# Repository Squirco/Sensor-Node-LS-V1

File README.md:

#Squirco Sensor Network Light Switch

Hardware files for Squirco Sensor Network Light Switch, as seen on Hackaday here:  
https://hackaday.io/project/3321-squirco-smart-home-system-sensor-network  
  
#Repository Contents
* **/Hardware-Main** - Eagle design files for the Logic and Power Supply boards (.sch and .brd)
* **/Hardware-Addon** - Eagle design files for the button, sensor, and programming adaptor boards (.sch and .brd)
* **/Hardware-3D** - 3D files for the enclosure. Designed to be 3D printed, tested with Form1+ and Shapeways/Sculpteo
* **/Hardware-Extras** - Contains BOM and other documents
* **/Firmware** - contains firmware files
  
#License Information
The hardware is released under <a href = "https://creativecommons.org/licenses/by-sa/4.0/">CC BY-SA 4.0</a>  
Hardware authors: Original Design by Steven @ Squirco
Distributed as-is; no warranty is given

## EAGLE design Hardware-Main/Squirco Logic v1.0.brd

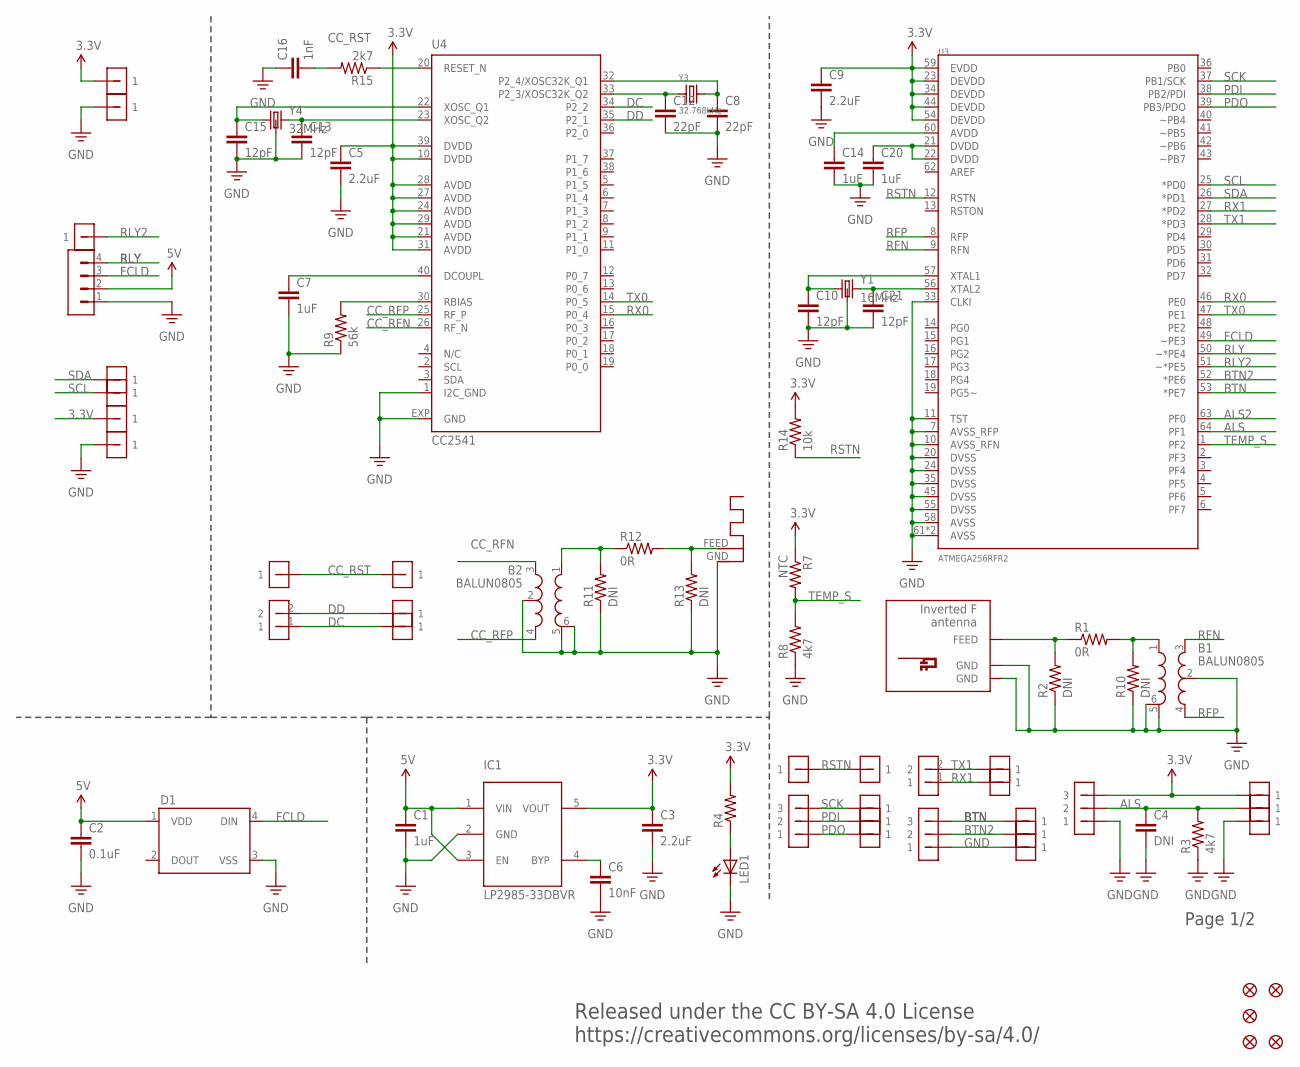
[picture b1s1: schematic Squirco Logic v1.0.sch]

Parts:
ANT1: ANTENNA; RN-ANT
ANT2: INVERTED_F_ANTENNA+5; DN007+5
B1, B2: BALUN0805; BALUN-2-4GHZ
C1, C7, C14, C20: 1uF; 0603-CAP
C2: 0.1uF; 0603-CAP
C3, C5, C9: 2.2uF; 0603-CAP
C4: DNI; 0603-CAP
C6: 10nF; 0603-CAP
C8, C12: 22pF; 0402-CAP
C10, C13, C15, C21: 12pF; 0402-CAP
C16: 1nF; 0603-CAP
D1: WS2812B
FID1, FID2, FID3, FID5, FID6: FIDUCIALUFIDUCIAL; MICRO-FIDUCIAL
IC1: LP2985-33DBVR; SOT23-5L
JP1: M02
LED1: LEDCHIP-LED0805; CHIP-LED0805
R1, R12: 0R; R0402
R2, R10, R11, R13: DNI; R0402
R3, R8: 4k7; R0603
R4: RESISTOR0603; 0603-RES
R7: NTC; R0402
R9: 56k; R0603
R14: 10k; R0603
R15: 2k7; R0603
U3: ATMEGA256RFR2; QFN-64
U4: CC2541; RHA_S-PVQFN-N40
U$4, U$6, U$25: M03
U$5: S04-4MM
U$7, U$8: M01
U$9: M02
U$10, U$11, U$12, U$13, U$14, U$15, U$16, U$17, U$18, U$19, U$20, U$21, U$22, U$23, U$24, U$26, U$27, U$30, U$31, U$34: S01C-4MM
U$32, U$33: S01-4MM
Y1: 16MHz; CRYSTAL-SMD-2.5X2-ABM10
Y3: 32.768kHz; ABS07
Y4: 32MHz; CRYSTAL-SMD-2.5X2-ABM10

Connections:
3.3V: C3.1, C5.1, C9.1, IC1.5 (VOUT), R4.2, R7.1, R14.2, U3.23 (DEVDD), U3.34 (DEVDD), U3.44 (DEVDD), U3.54 (DEVDD), U3.59 (EVDD), U4.10 (DVDD), U4.21 (AVDD), U4.24 (AVDD), U4.27 (AVDD), U4.28 (AVDD), U4.29 (AVDD), U4.31 (AVDD), U4.39 (DVDD), U$20.P$1, U$25.3, U$26.P$1, U$30.P$1
5V: C1.1, C2.1, D1.1 (VDD), IC1.1 (VIN), IC1.3 (EN), U$5.2
ALS: C4.1, R3.2, U3.64 (PF1), U$25.2, U$31.P$1
ALS2: U3.63 (PF0)
BTN: U3.53 (*PE7), U$6.3, U$22.P$1
BTN2: U3.52 (*PE6), U$6.2, U$23.P$1
CC_RFN: B2.3, U4.26 (RF_N)
CC_RFP: B2.4, U4.25 (RF_P)
CC_RST: C16.2, R15.2, U$8.1, U$17.P$1
DC: U4.34 (P2_2), U$9.1, U$19.P$1
DD: U4.35 (P2_1), U$9.2, U$18.P$1
FCLD: D1.4 (DIN), U3.49 (~PE3), U$5.3
GND: ANT1.GND, ANT2.GND, ANT2.GND@1 (GND), B1.2, B1.5, B1.6, B2.2, B2.5, B2.6, C1.2, C2.2, C3.2, C4.2, C5.2, C6.2, C7.2, C8.2, C9.2, C10.2, C12.2, C13.2, C14.2, C15.2, C16.1, C20.2, C21.2, D1.3 (VSS), IC1.2 (GND), LED1.C, R2.1, R3.1, R8.1, R9.1, R10.1, R11.1, R13.1, U3.7 (AVSS_RFP), U3.10 (AVSS_RFN), U3.11 (TST), U3.20 (DVSS), U3.24 (DVSS), U3.33 (CLKI), U3.35 (DVSS), U3.45 (DVSS), U3.55 (DVSS), U3.58 (AVSS), U3.61 (AVSS), U3.PADDLE (AVSS), U4.1 (I2C_GND), U4.EXP (GND), U$5.1, U$6.1, U$21.P$1, U$25.1, U$27.P$1, U$32.P$1, U$33.P$1, Y1.P$2 (GND), Y1.P$4 (GND), Y4.P$2 (GND), Y4.P$4 (GND)
unnamed: C10.1, U3.57 (XTAL1), Y1.P$1 (1)
unnamed: C21.1, U3.56 (XTAL2), Y1.P$3 (2)
unnamed: LED1.A, R4.1
unnamed: ANT2.FEED, R1.1, R2.2
unnamed: C6.1, IC1.4 (BYP)
unnamed: C7.1, U4.40 (DCOUPL)
unnamed: C20.1, U3.21 (DVDD), U3.22 (DVDD)
unnamed: C14.1, U3.60 (AVDD)
unnamed: R9.2, U4.30 (RBIAS)
unnamed: B2.1, R11.2, R12.1
unnamed: ANT1.FEED, R12.2, R13.2
unnamed: C15.1, U4.22 (XOSC_Q1), Y4.P$1 (1)
unnamed: C13.1, U4.23 (XOSC_Q2), Y4.P$3 (2)
unnamed: C8.1, U4.32 (P2_4/XOSC32K_Q1), Y3.2
unnamed: B1.1, R1.2, R10.2
unnamed: C12.1, U4.33 (P2_3/XOSC32K_Q2), Y3.1
unnamed: R15.1, U4.20 (RESET_N)
N/C: U4.4 (N/C)
PDI: U3.38 (PB2/PDI), U$4.2, U$13.P$1
PDO: U3.39 (PB3/PDO), U$4.1, U$14.P$1
RFN: B1.3, U3.9 (RFN)
RFP: B1.4, U3.8 (RFP)
RLY: U3.50 (~*PE4), U$5.4
RLY2: U3.51 (~*PE5), U$34.P$1
RSTN: R14.1, U3.12 (RSTN), U$7.1, U$11.P$1
RX0: U3.46 (PE0), U4.15 (P0_4)
RX1: JP1.1, U3.27 (*PD2), U$16.P$1
SCK: U3.37 (PB1/SCK), U$4.3, U$12.P$1
SCL: U3.25 (*PD0), U$24.P$1
SDA: U3.26 (*PD1), U$10.P$1
TEMP_S: R7.2, R8.2, U3.1 (PF2)
TX0: U3.47 (PE1), U4.14 (P0_5)
TX1: JP1.2, U3.28 (*PD3), U$15.P$1

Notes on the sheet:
Page 1/2
Released under the CC BY-SA 4.0 License https://creativecommons.org/licenses/by-sa/4.0/

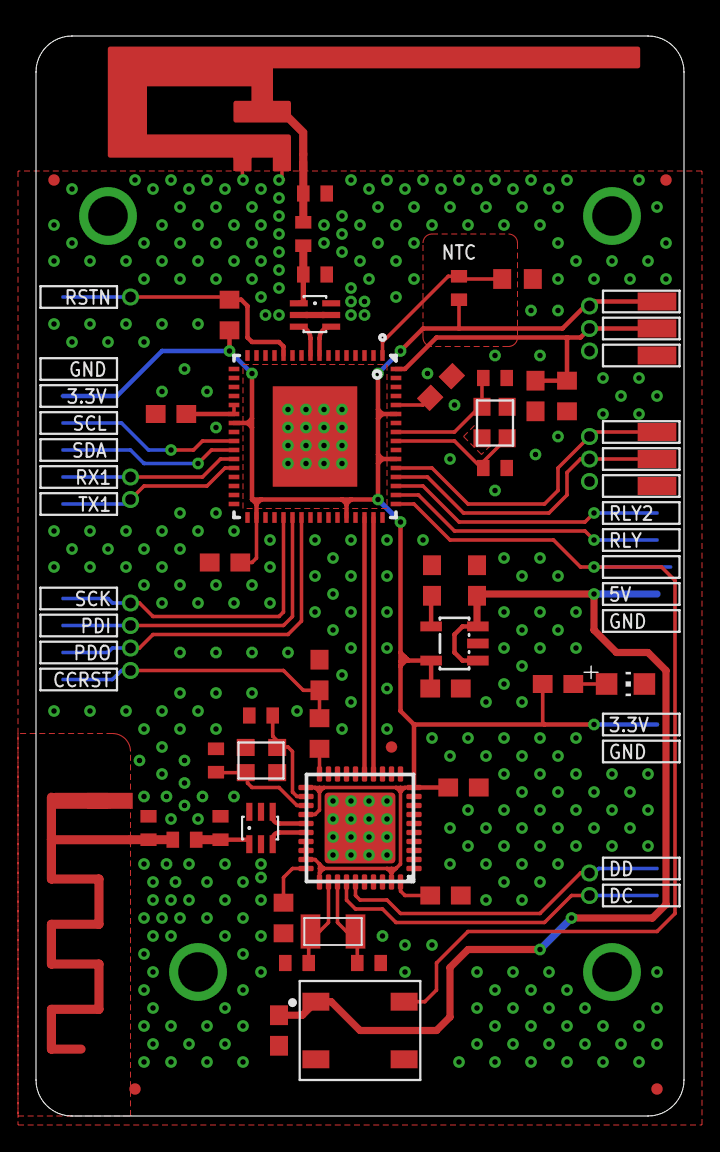
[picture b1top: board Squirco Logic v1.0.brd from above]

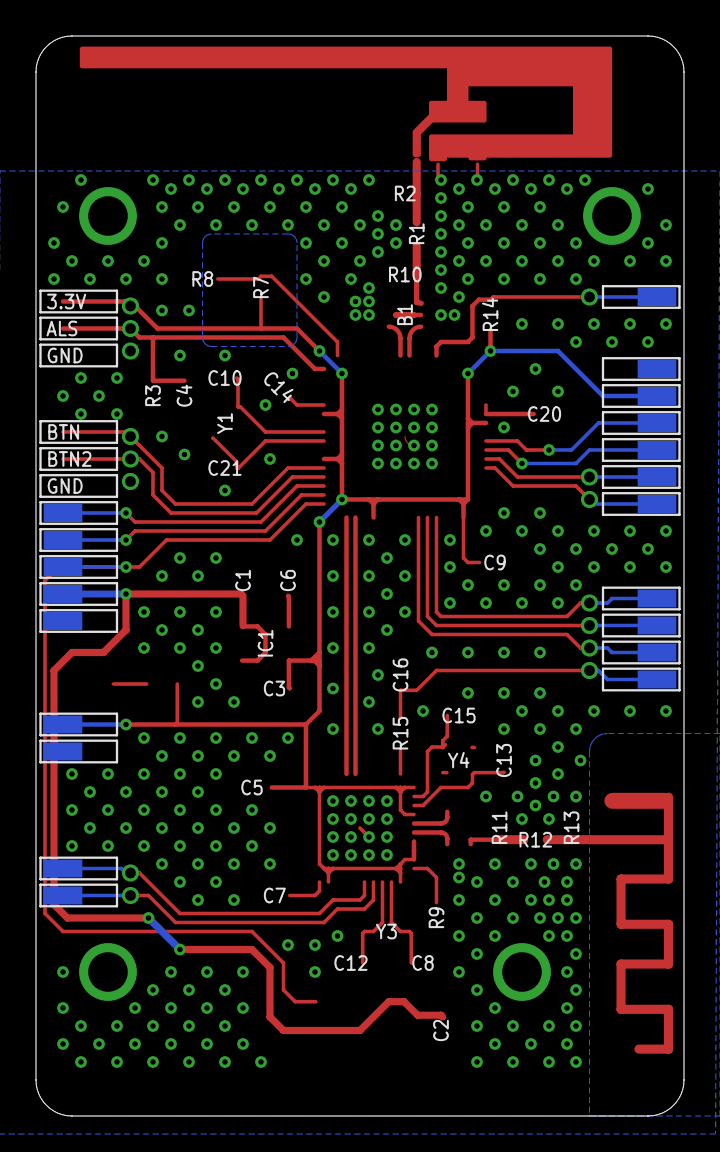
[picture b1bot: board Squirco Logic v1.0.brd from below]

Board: 2 copper layers, 36.0 x 60.0 mm, 77 parts (17 on the bottom side), 44 nets.

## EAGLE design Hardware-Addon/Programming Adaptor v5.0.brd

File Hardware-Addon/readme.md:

#Squirco Sensor Light Switch Addons
Button board is designed for 1.6mm thickness. Ambient light sensor board is designed for 1.6mm thickness or below, ideally as thin as possible.

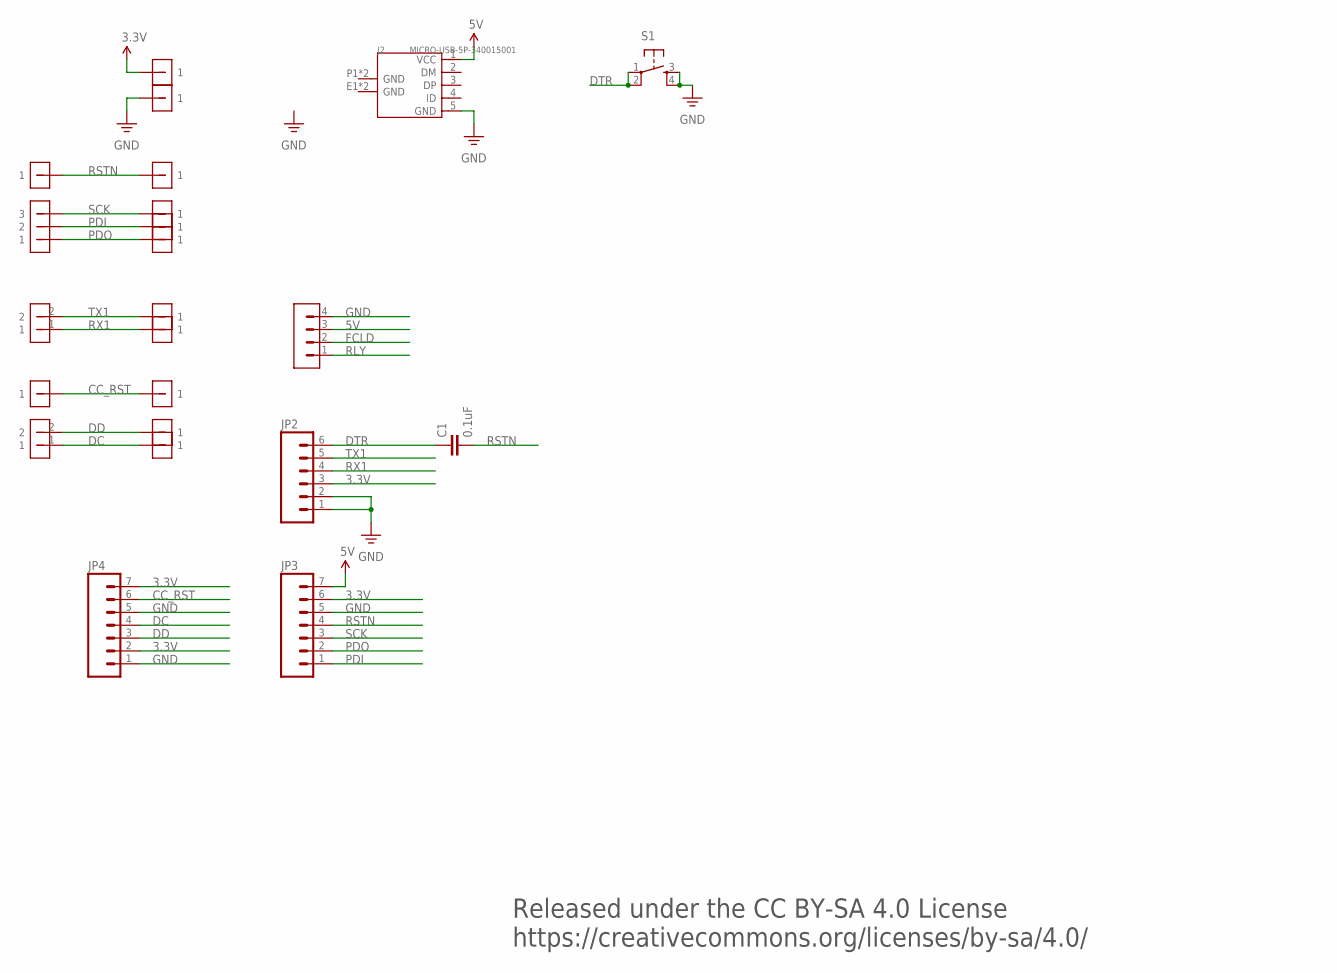
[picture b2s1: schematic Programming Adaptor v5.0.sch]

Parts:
C1: 0.1uF; 0603-CAP
J2: MICRO-USB-5P-340015001; B-SMD-5P
JP1: M02
JP2: M06LOCK; 1X06_LOCK
JP3, JP4: M07; 1X07
S1: TAC_SWITCHSMD; TACTILE-SWITCH-SMD
U$4: M03
U$5: S04-4MM
U$7, U$8: M01
U$9: M02
U$11, U$12, U$13, U$14, U$15, U$16, U$17, U$18, U$19, U$20, U$21: S01C-4MM

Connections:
3.3V: JP2.3, JP3.6, JP4.2, JP4.7, U$20.P$1
5V: J2.1 (VCC), JP3.7, U$5.3
CC_RST: JP4.6, U$8.1, U$17.P$1
DC: JP4.4, U$9.1, U$19.P$1
DD: JP4.3, U$9.2, U$18.P$1
DTR: C1.1, JP2.6, S1.1, S1.2
FCLD: U$5.2
GND: J2.5 (GND), JP2.1, JP2.2, JP3.5, JP4.1, JP4.5, S1.3, S1.4, U$5.4, U$21.P$1
PDI: JP3.1, U$4.2, U$13.P$1
PDO: JP3.2, U$4.1, U$14.P$1
RLY: U$5.1
RSTN: C1.2, JP3.4, U$7.1, U$11.P$1
RX1: JP1.1, JP2.4, U$16.P$1
SCK: JP3.3, U$4.3, U$12.P$1
TX1: JP1.2, JP2.5, U$15.P$1

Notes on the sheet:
Released under the CC BY-SA 4.0 License https://creativecommons.org/licenses/by-sa/4.0/

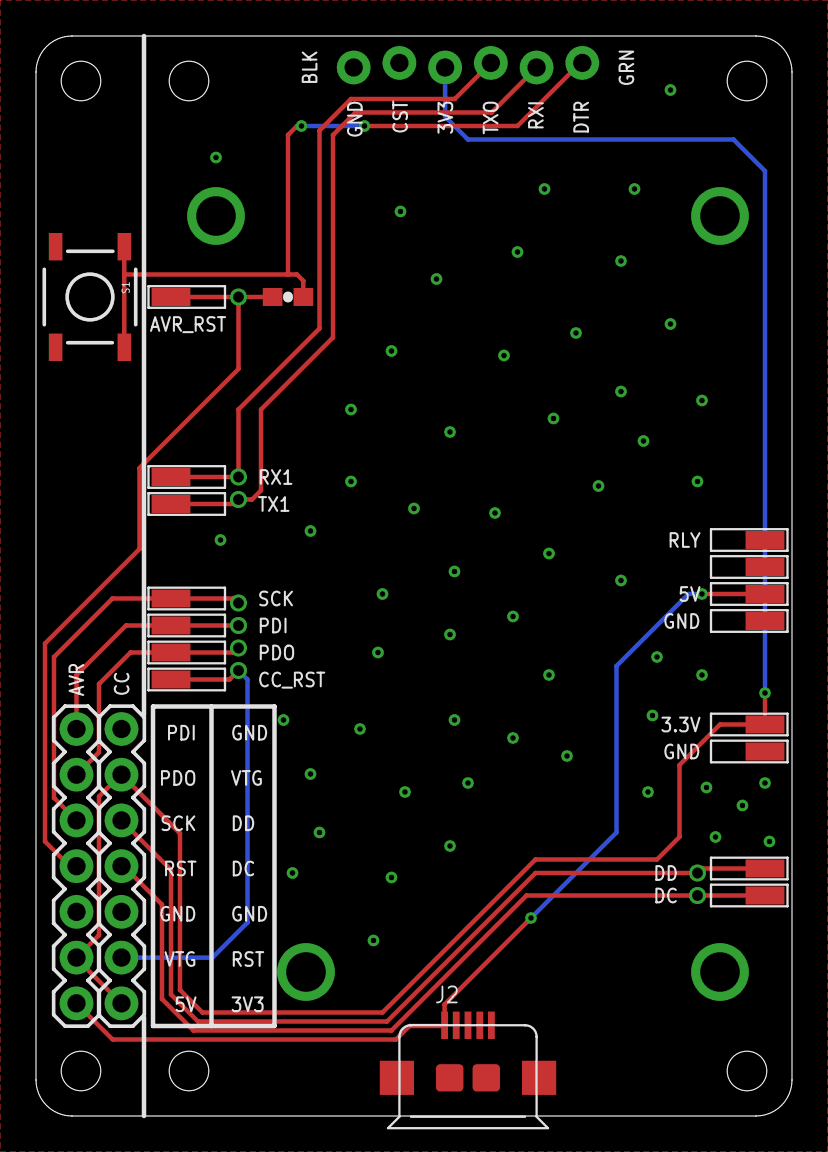
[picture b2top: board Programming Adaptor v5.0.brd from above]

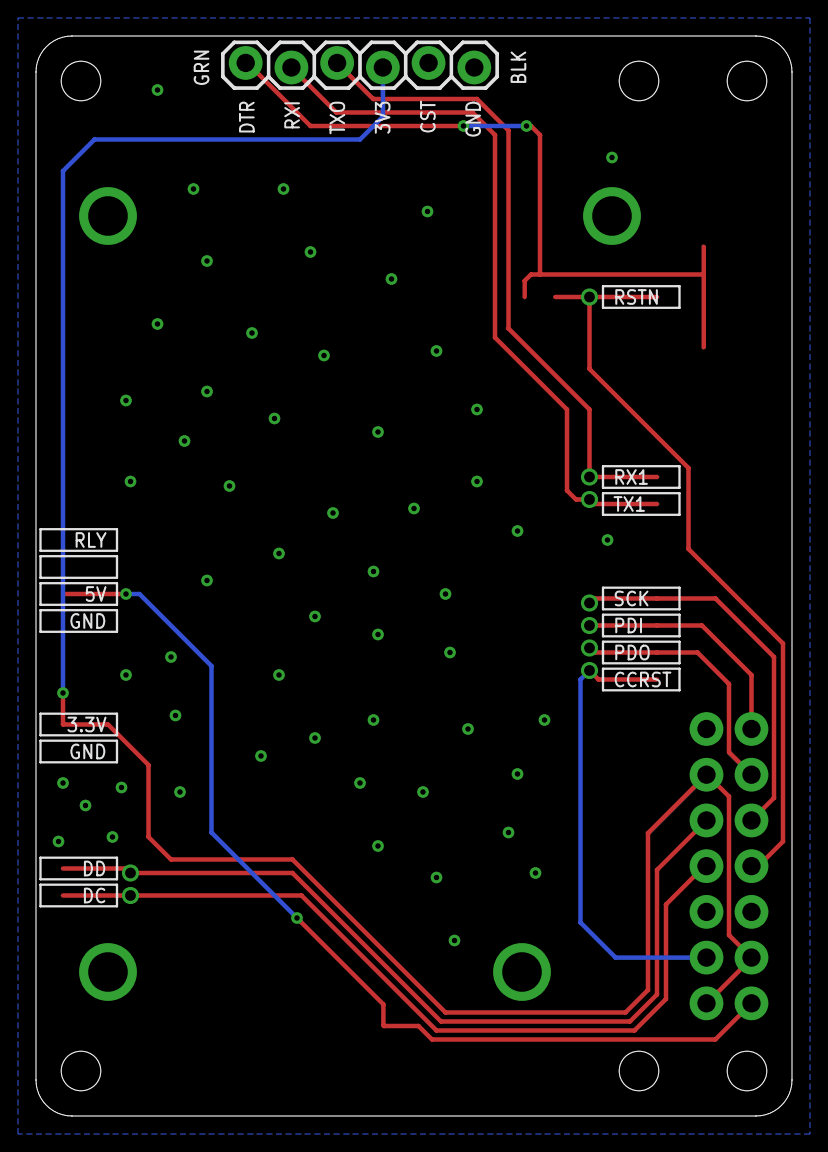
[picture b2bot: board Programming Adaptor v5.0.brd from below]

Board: 2 copper layers, 42.0 x 60.0 mm, 23 parts (2 on the bottom side), 13 nets.

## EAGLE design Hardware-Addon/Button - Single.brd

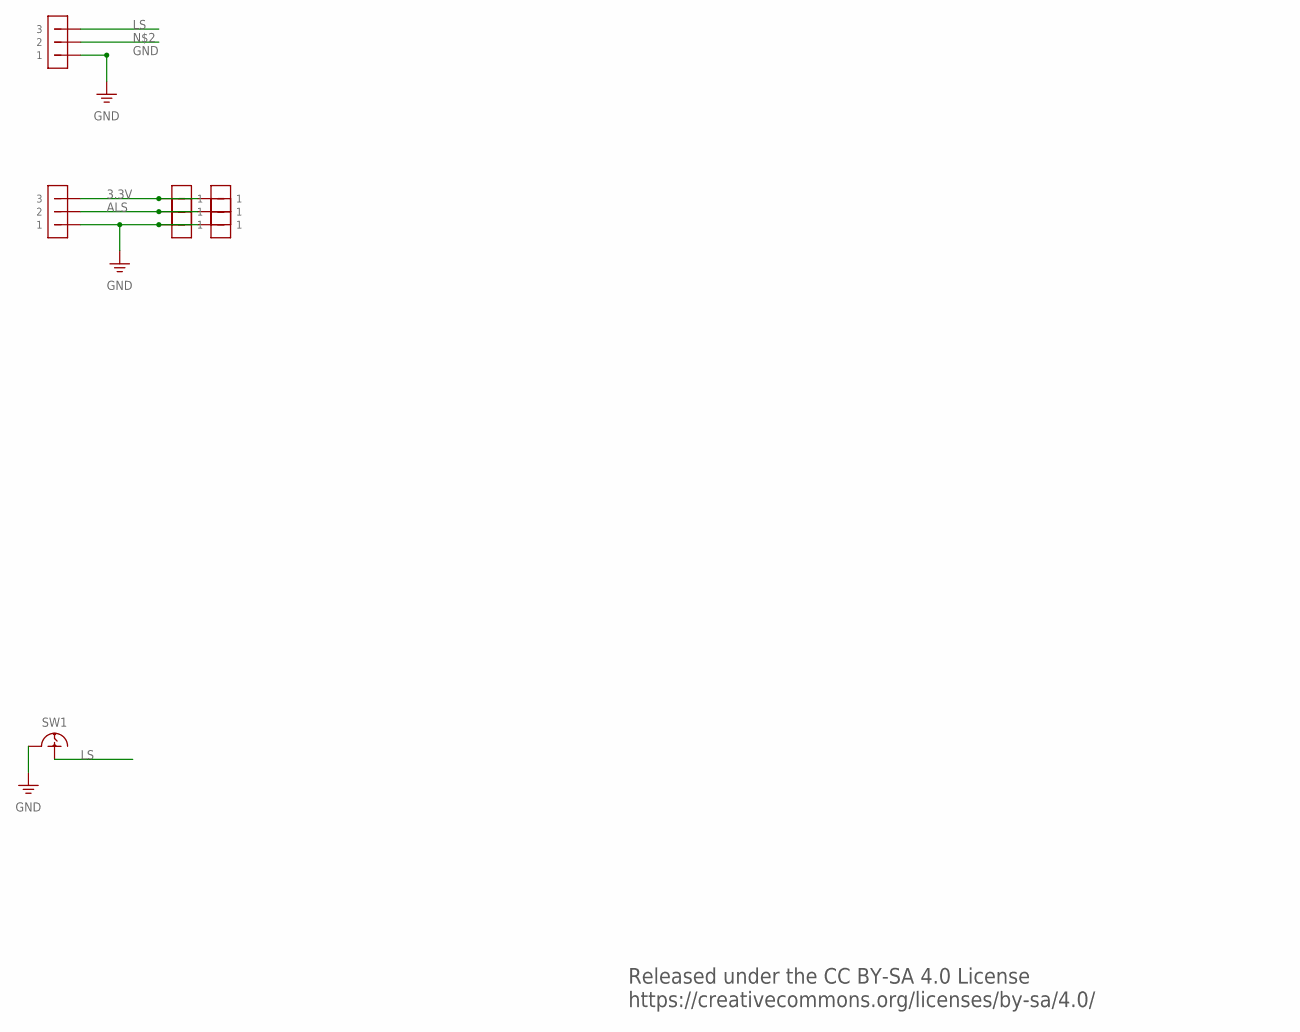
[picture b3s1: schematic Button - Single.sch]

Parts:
SW1: U12390; UFTCGX12
U$1, U$2: M03
U$3, U$4, U$5, U$6, U$7, U$8: S01-4MM

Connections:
3.3V: U$1.3, U$3.P$1, U$6.P$1
ALS: U$1.2, U$4.P$1, U$7.P$1
GND: SW1.GND, U$1.1, U$2.1, U$5.P$1, U$8.P$1
LS: SW1.SIG, U$2.3

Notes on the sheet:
Released under the CC BY-SA 4.0 License https://creativecommons.org/licenses/by-sa/4.0/

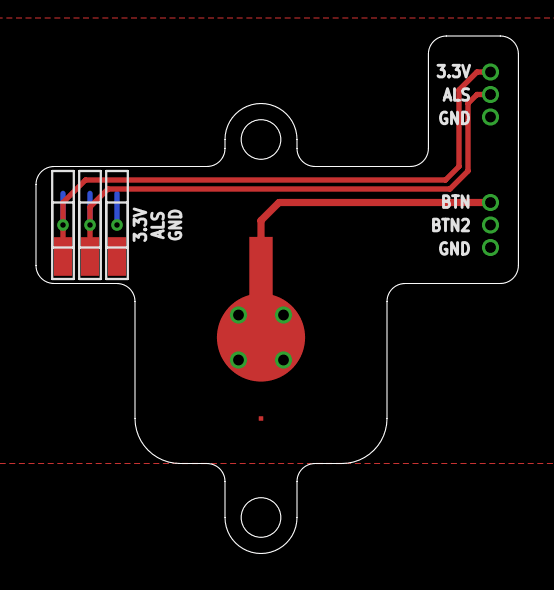
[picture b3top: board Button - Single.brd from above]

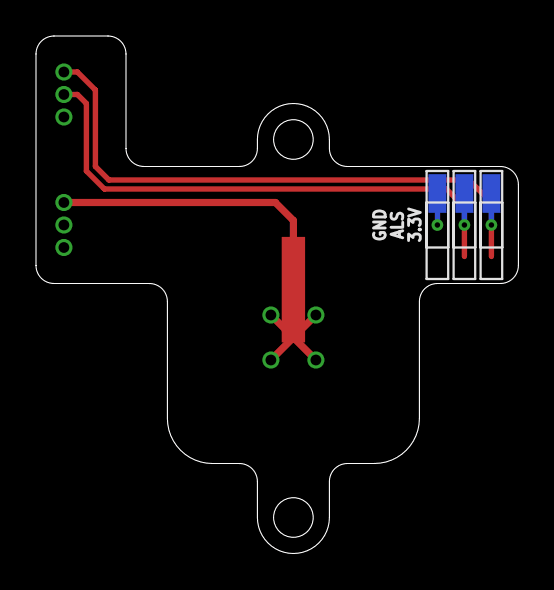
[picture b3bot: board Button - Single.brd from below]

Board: 2 copper layers, 26.8 x 28.8 mm, 9 parts (3 on the bottom side), 4 nets.

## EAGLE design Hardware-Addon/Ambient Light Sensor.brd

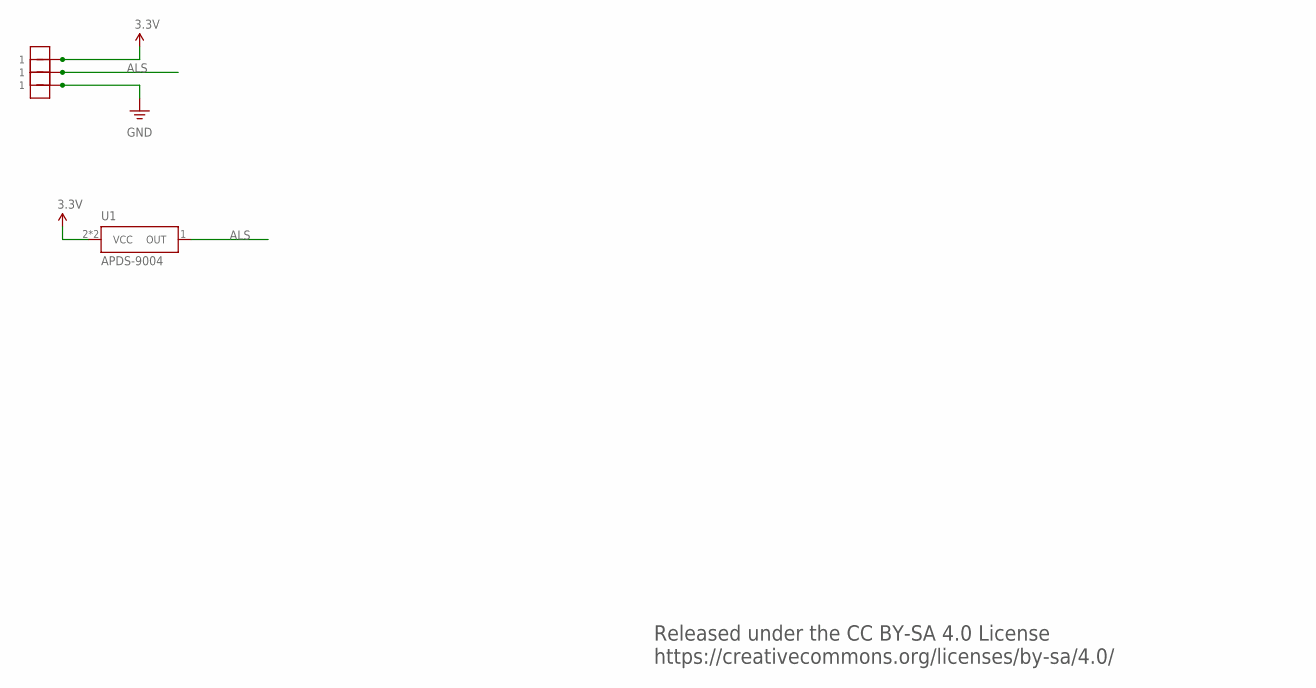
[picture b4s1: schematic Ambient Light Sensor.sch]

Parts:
U1: ADPS-9004; APDS-9004
U$2, U$3, U$4: S01-4MM

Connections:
3.3V: U1.2 (VCC), U1.3 (VCC), U$2.P$1
ALS: U1.1 (OUT), U$3.P$1
GND: U$4.P$1

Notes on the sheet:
Released under the CC BY-SA 4.0 License https://creativecommons.org/licenses/by-sa/4.0/

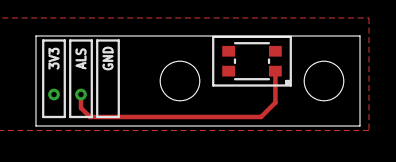
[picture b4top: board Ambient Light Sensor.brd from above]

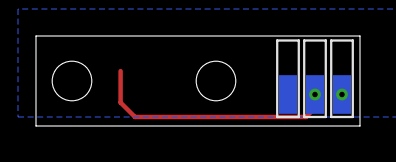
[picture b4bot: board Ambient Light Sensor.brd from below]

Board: 2 copper layers, 18.0 x 5.0 mm, 4 parts (3 on the bottom side), 2 nets.

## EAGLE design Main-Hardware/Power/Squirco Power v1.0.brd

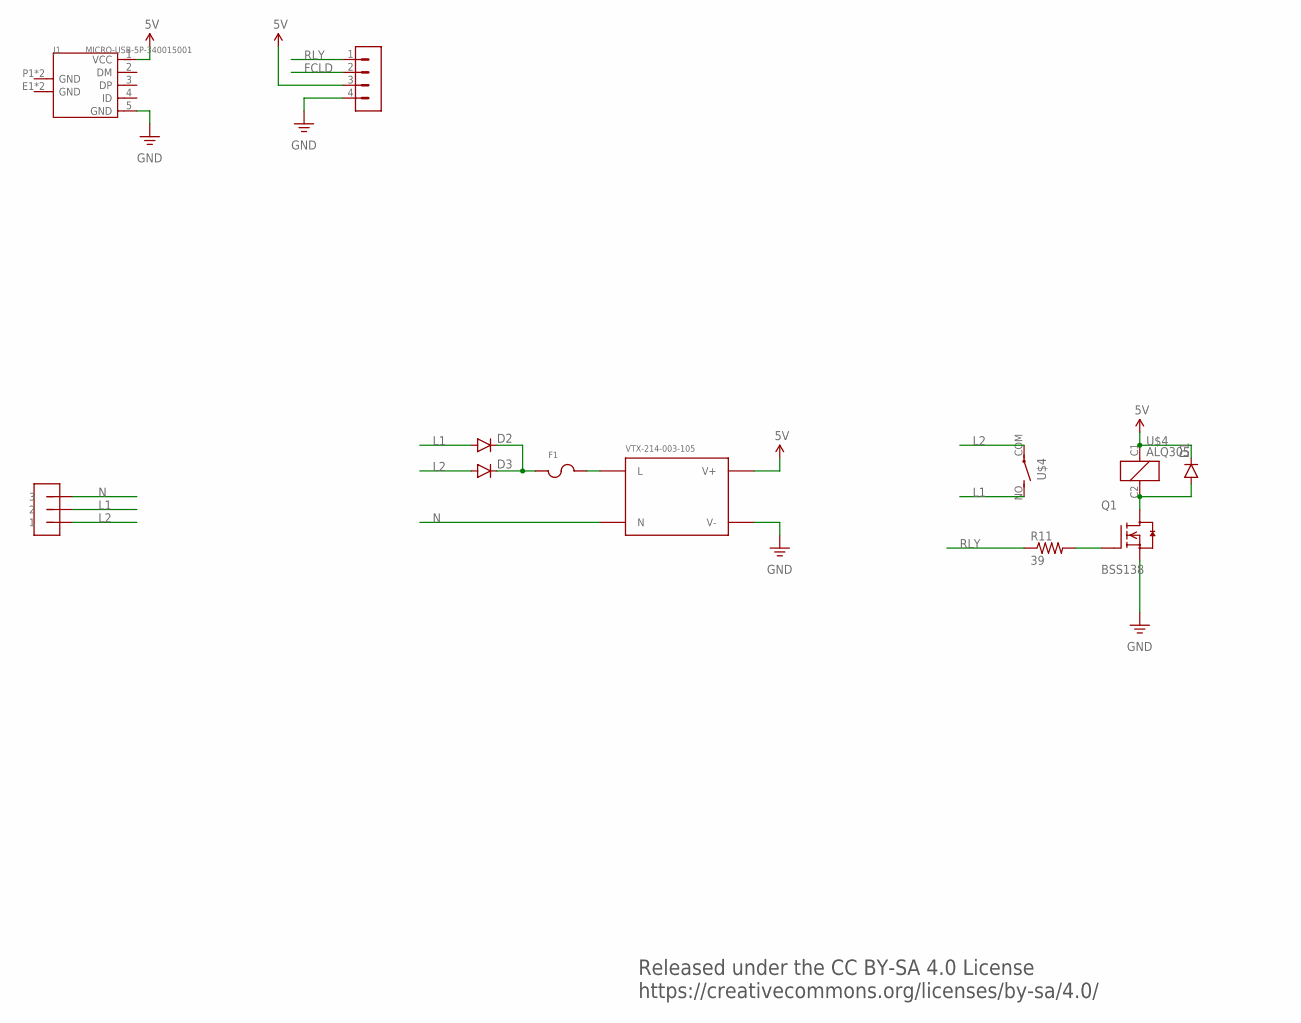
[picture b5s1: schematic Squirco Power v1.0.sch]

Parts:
D1, D2, D3: DIODESMB; SMB-DIODE
F1: UMT250
J1: MICRO-USB-5P-340015001; B-SMD-5P
JP2: LSF-SMT5; LF-SMT5
Q1: BSS138; SOT23
R11: 39; 0603-RES
U$1: VTX-214-003-105; VTX-214-003-1XX
U$3: S04-4MM
U$4: ALQ305

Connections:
5V: D1.C, J1.1 (VCC), U$1.3 (V+), U$3.3, U$4.C1 (1)
FCLD: U$3.2
GND: J1.5 (GND), Q1.2 (S), U$1.4 (V-), U$3.4
L1: D2.A, JP2.3 (2), JP2.4 (2), U$4.NO (S)
L2: D3.A, JP2.1, JP2.2 (1), U$4.COM
N: JP2.5 (3), JP2.6 (3), U$1.1 (N)
unnamed: F1.P$2, U$1.2 (L)
unnamed: Q1.1 (G), R11.2
unnamed: D2.C, D3.C, F1.P$1
unnamed: D1.A, Q1.3 (D), U$4.C2 (2)
RLY: R11.1, U$3.1

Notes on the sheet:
Released under the CC BY-SA 4.0 License https://creativecommons.org/licenses/by-sa/4.0/

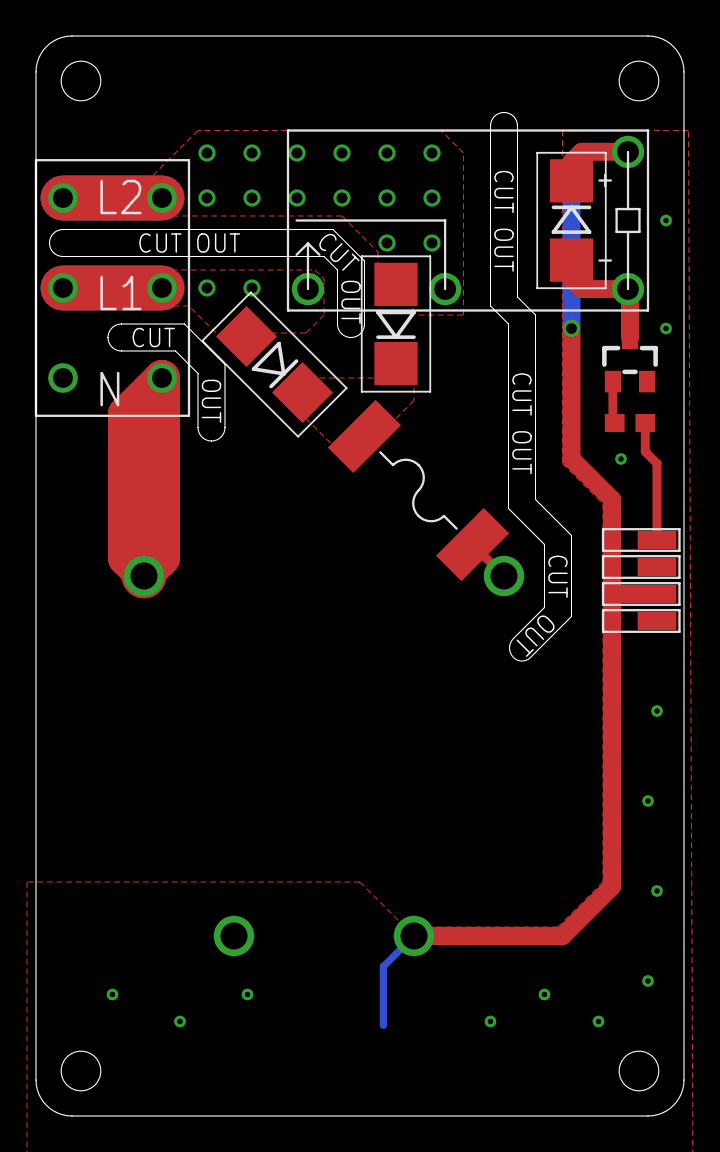
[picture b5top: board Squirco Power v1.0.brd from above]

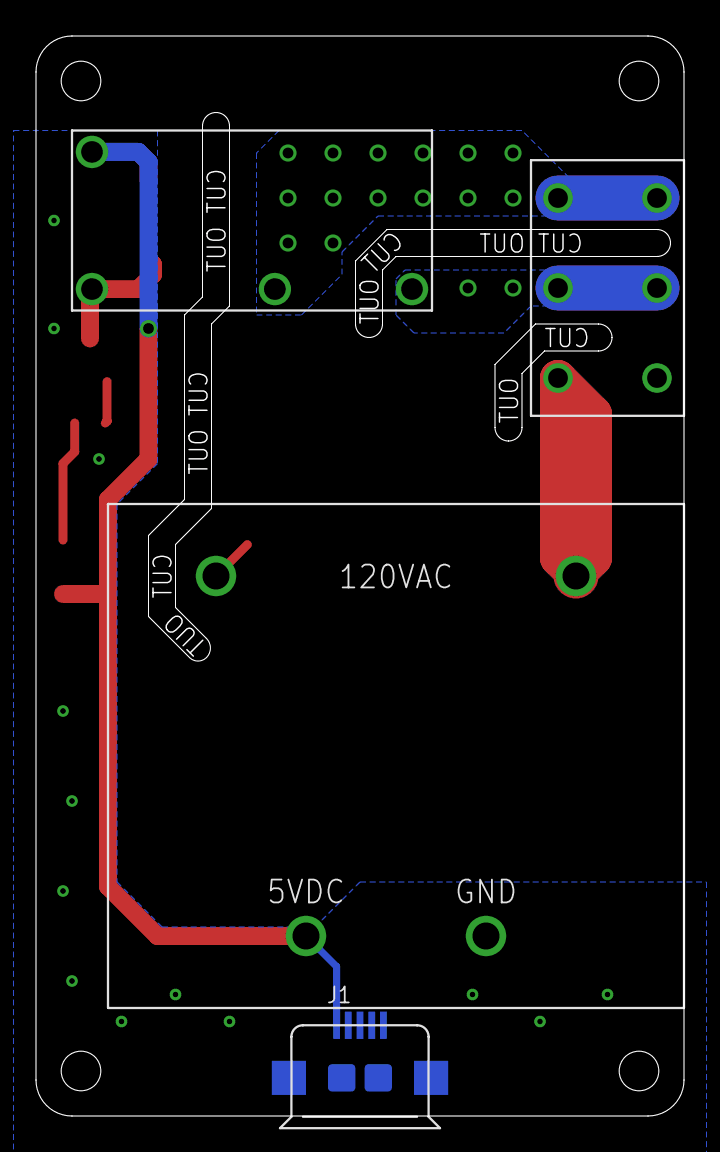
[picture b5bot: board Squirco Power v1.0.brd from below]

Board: 2 copper layers, 36.0 x 60.0 mm, 11 parts (2 on the bottom side), 10 nets.

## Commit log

2015-06-08 Create <Main Hardware>
2015-06-08 Create readme.
2015-06-08 3D Enclosure Files
2015-06-08 Revert "3D Enclosure Files"
    This reverts commit 6feb40abfe3c21414d5d52db9328c61a6ee889bb.
2015-06-08 Testing GitHub
2015-06-08 Logic and Power
2015-06-08 Logic Board v1.0
2015-06-08 Power Board v1.0
2015-06-08 3D Files Added
2015-06-08 Button and ALS added
2015-06-20 Added Programming Adaptor
2015-06-20 Added new directory
2015-06-21 Merge remote-tracking branch 'origin/master'
    Conflicts:
    Hardware-Extras/README.md
2015-06-21 Added BOM
2015-08-17 Added firmware in progress

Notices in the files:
Hardware-Main/Squirco Logic v1.0.brd:
Copyright 2015 Squirco
parts and their libraries:
SparkFun-Connectors: Licensing: Creative Commons ShareAlike 4.0 International - https://creativecommons.org/licenses/by-sa/4.0
m-pad-2.1: License : GNU General Public License version 2 (see bottom)
